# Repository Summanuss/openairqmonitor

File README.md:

# Open AirQ Monitor

## Table of Contents
- [Open AirQ Monitor](#open-airq-monitor)
  - [Table of Contents](#table-of-contents)
  - [Overview](#overview)
  - [Description](#description)
  - [Key Features](#key-features)
  - [Technical Specifications](#technical-specifications)
  - [Project Structure](#project-structure)
  - [Hardware Documentation](#hardware-documentation)
  - [Pinout \& Connectors](#pinout--connectors)
  - [Getting Started](#getting-started)
    - [Opening the KiCad project](#opening-the-kicad-project)
    - [Generating fabrication files](#generating-fabrication-files)
    - [Flashing the firmware](#flashing-the-firmware)
  - [Ordering \& Fabrication Guidelines](#ordering--fabrication-guidelines)
  - [Test Firmware](#test-firmware)
  - [Known Issues \& Future Improvements](#known-issues--future-improvements)
  - [Safety Notes](#safety-notes)
  - [Revision History](#revision-history)
  - [License](#license)
  - [Acknowledgments](#acknowledgments)
  - [Contact](#contact)

## Overview
- **Description:** STM32 based custom-board to monitor temperature, humidity and VOC
- **Status:** Stable - Revision 2.0
- **License:** Apache-2.0 license

## Description
Open AirQ Monitor is a very simple STM32 custom PCB with a temperature/humidity sensor and a
VOC sensor. It's goal is to be a consumer / gadget product which you can keep in your bedroom,
rather than a professional industrial solution to monitor ambient parameters.
Given that, I decided to use an LCD TFT RGB display so the firmware application can be more
"fancy" and "nice". <br>
As an hobbistic project, I wanted it to be as cheap and easy to design as possible. <br>
This can be seen as a starting point to build a more advanced product with more functionality,
so feel free to fork the repo and customize it as you like!

## Key Features
- LCD TFT [128x160 px] Display
- Dimmable display backlight
- USB-C powered (5V)
- Push-button as a general input or EXTI
- Real-time temperature and humidity measurement
- Real-time VOC measurement

## Technical Specifications
| Parameter | Value |
| :--- | :--- |
| **Input Voltage** | 5V |
| **Typical Current Draw** | **TODO** (e.g. ~xx mA idle / xx mA peak) |
| **Microcontroller / Core** | STM32L431CCT6TR |
| **Microcontroller / RAM** | 64 KB |
| **Microcontroller / FLASH** | 256 KB |
| **VOC Sensor** | SGP40-D-R4 |
| **Temp/Humidity Sensor** | SHT40-AD1B-R2 |
| **TFT Display** | ER-TFT018-3 |
| **Dimensions** | 60x40 mm |
| **Mounting Holes** | M2 |

## Project Structure
```text
├── docs/             # Documentation, schematics PDF, and renders
├── fabrication/      # Production files (Gerbers, BOM, Pick & Place)
├── design/           # KiCad project source files
├── exported          # .step, BOM, ...
├── LICENSE           # License file
└── README.md         # Project documentation
```

## Hardware Documentation
Check the docs/ folder.

## Pinout & Connectors
For the complete pinout check the schematic.
| Pin | Function | Description | Direction
| :--- | :--- | :--- | :--- |
| PA1 | SPI_CLK | SPI Clock Signal | Out |
| PA3 | BUTTON_IN | External Button Signal | In |
| PA4 | DC_DISPLAY | Data / Command Display Signal | Out |
| PA5 | RST_DISPLAY | Display Reset Signal | Out |
| PA6 | CS_DISPLAY | Display Chip Select Signal | Out |
| PA7 | SPI_MOSI | Display Serial Data Signal | Out |
| PA8 | BCK_LIGHT_DISPLAY | Display Backlight Signal | Out |
| PA9 | I2C_SCL | SCL Line of I2C bus | Out |
| PA10 | I2C_SDA | SDA Line of I2C bus | In / Out |
| PA11 | SWDIO | Serial Wire Data Signal | In / Out |
| PA14 | SWCLK | Serial Wire Protocol Clock Signal | In |
| PB3 | SWO | Serial Wire Protocol Output Signal | Out |

## Getting Started
 
### Opening the KiCad project
1. Install [KiCad 10.0](https://www.kicad.org/download/) or later.
2. Clone this repository.
3. Custom symbol files should be automatically embedded (KiCad versione > 6). If this is not the case, open an issue an I'll fix it ASAP.

### Generating fabrication files
1. Open the PCB editor in KiCad.
2. Export Gerbers, drill files, and Pick & Place using KiCad's built-in plotter (or the AISLER plugin, see [Ordering & Fabrication Guidelines](#ordering--fabrication-guidelines)).
3. Upload the generated files in your chosen manufacturer website (es. AISLER)
4. Check the correctness of the layout in the preview before ordering!

### Flashing the firmware
1. Connect an SWD programmer (e.g. ST-Link V2/V3) to the `SWDIO`/`SWCLK`/`SWO` pins.
2. Build and flash the firmware from the [Test Firmware](#test-firmware) repository following its own instructions.
3. Power the board via USB-C (5V) once flashing is complete.

## Ordering & Fabrication Guidelines
The chosen manufacturer is AISLER and every constraints in the layout that I used is based on their specifications.<br>
I used the AISLER plugin for KiCad to export all fabrication files. Just for reference, I created them manually in
fabrication directory. <br>
However, I didn't double checked those and a further analysis is suggested.
Also, the PCB was manually assembled by me and no assembly services were used from the manufacturer.

## Test Firmware
Test firmware written in C is provided [here](https://github.com/Summanuss/openairqmonitor_testfw.git) <br>
More information about it are provided in the linked repository.

## Known Issues & Future Improvements
- The SHT40 sensor is not perfectly thermally decoupled from the PCB and its reading can be a bit altered from the heat generated from the display and the rest of the PCB.
- The flashing and debugging pins are permanently soldered on the PCB which is not optimal.
<br>Ideas for revision 3.0:
- Correct the known issues.
- Provide the support for a battery powered device.

## Safety Notes
- The board is powered via USB-C at 5V - use a standard certified USB-C cable/power source.
- Use the SWD connector interface **ONLY** for flashing and debug.

## Revision History
- **v2.0:** Final and stable version
- **v1.0:** First working prototype

## License
Distributed under the Apache-2.0 License. See `LICENSE` for more information.

## Acknowledgments
I would like to thanks my friends which worked on the final firmware product and device enclouse:
- D.G.
- A.B.

## Contact
Mail: serafin.jacopo99@gmail.com

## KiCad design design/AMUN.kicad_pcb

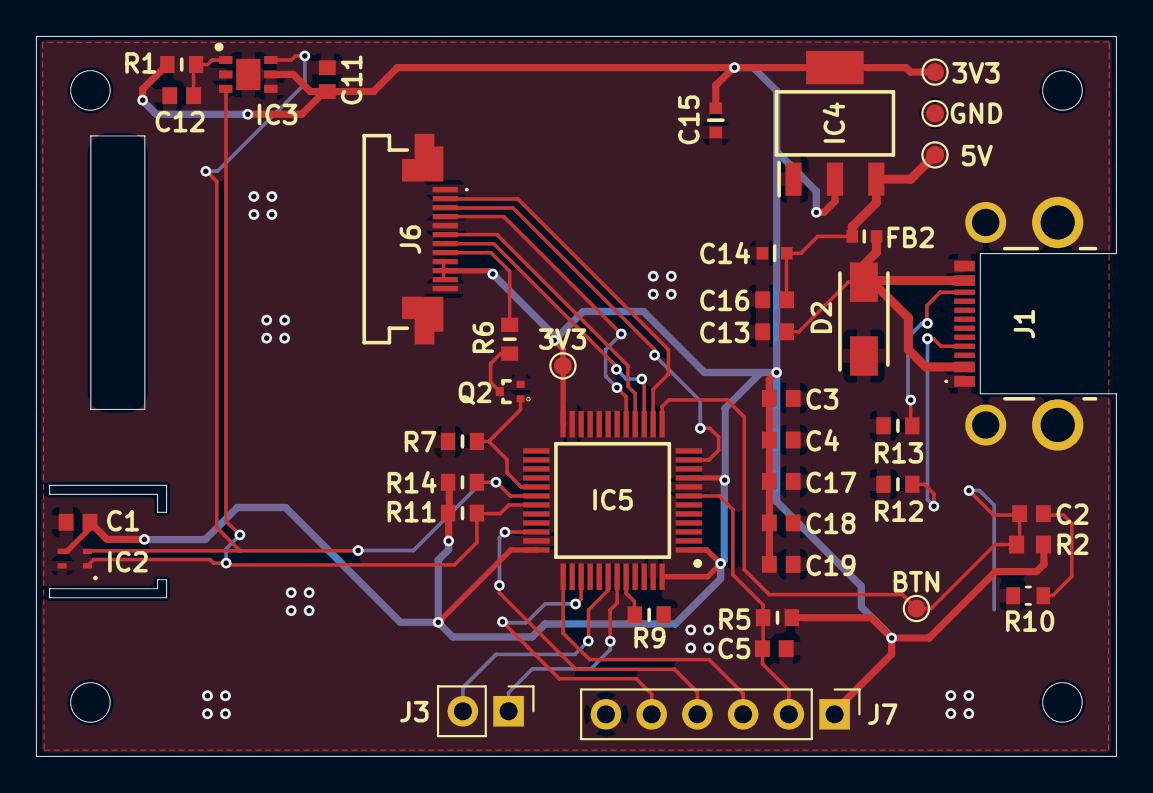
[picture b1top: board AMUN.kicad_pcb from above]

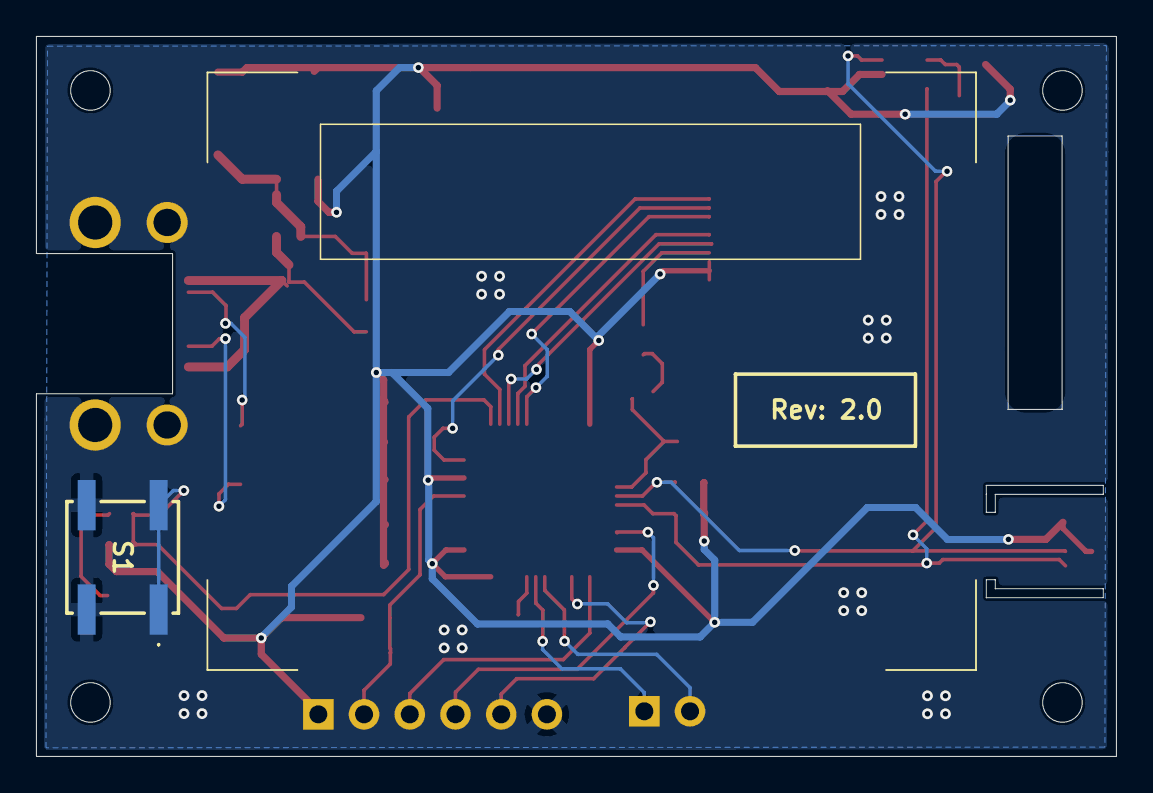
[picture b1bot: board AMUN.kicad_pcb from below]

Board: 2 copper layers, 60.0 x 40.0 mm, 47 parts (2 on the bottom side), 26 nets.

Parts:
3V3, 3V3#2: 3V3; TestPoint_Pad_D1.0mm
5V: 5V; TestPoint_Pad_D1.0mm
BTN: BTN; TestPoint_Pad_D1.0mm
C1, C2, C3, C4, C5, C17, C18, C19: 100nF; CAPC1608X90N
C11, C12: 1uF; CAPC1608X90N
C13, C16: 2.2uF; CAPC1608X90N
C14: 10uF; GRM18x
C15: 22uF; GRM18x
D2: SMAJ6.5CA_TR7; DIOM5127X250N
FB2: BLM18PG330SH1D; BLM18SP221SN1B
GND: GND; TestPoint_Pad_D1.0mm
H1, H2, H3, H4: MountingHole; MountingHole_2.2mm_M2_DIN965
IC2: SHT40-AD1B-R2; SHT40AD1BR2
IC3: SGP40-D-R4; SON80P244X244X95-7N
IC4: AZ1117CH-3.3TRG1; SOT230P700X180-4N
IC5: STM32L431CCT6TR; QFP50P900X900X160-48N
J1: UJ20-C-H-G-MSMT-4B-P16-TR; UJ20CHGMSMT4BP16TR
J3: Conn_01x02_Pin; PinHeader_1x02_P2.54mm_Vertical
J6: SFV12R-1STBE1HLF; SFV12R1STBE1HLF
J7: Conn_01x06; PinHeader_1x06_P2.54mm_Vertical
Q2: SSM3K16FV,L3F; VESM_SOT-723_
R1: RC0603FR-134R7L; RESC1608X55N
R2: 4.7K; RESC1608X50N
R5, R7, R9, R11, R14: 10K; RESC1608X55N
R6: 10; RESC1608X55N
R10: 100; RESC1608X60N
R12, R13: 5.1K; RESC1608X55N
S1: EL2_52_35J_LFS; EL25235JLFS
U2: ER-TFT018-3

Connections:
+3V3: 3V3.1 (1_1), 3V3#2.1 (1_1), C1.1, C3.1, C4.1, C11.1, C15.1, C17.1, C18.1, C19.1, IC2.3 (VDD), IC3.5 (VDDH), IC4.2 (OUTPUT), IC4.4 (VOUT), IC5.1 (VBAT), IC5.9 (VDDA/VREF+), IC5.24 (VDD_1), IC5.36 (VDD_2), IC5.48 (VDD_3), J6.9, J6.10, J6.11, J7.1, R1.2, R2.2, R5.2, R11.2, R14.2
+5V: 5V.1 (1_1), C14.1, C16.1, FB2.2, IC4.3 (INPUT)
/BCK_LIGHT: IC5.29 (PA8), Q2.1 (G), R7.1
/CS_DISPLAY: IC5.16 (PA6), J6.6
/DC_DISPLAY: IC5.14 (PA4), J6.2
/Display/LEDK: J6.8, R6.2
/I2C_SCL: IC2.2 (SCL), IC3.6 (SCL), IC5.30 (PA9), R14.1
/I2C_SDA: IC2.1 (SDA), IC3.3 (SDA), IC5.31 (PA10), R11.1
/MCU/BUTTON: BTN.1 (1_1), C2.1, IC5.13 (PA3), R2.1, S1.1 (COM_1), S1.2 (COM_2)
/MCU/MCU_BOOT0: IC5.44 (PH3/BOOT0), R9.2
/MCU/MCU_NRST: C5.1, IC5.7 (NRST), J7.2, R5.1
/MCU/MCU_SWCLK: IC5.37 (PA14), J7.3
/MCU/MCU_SWDIO: IC5.34 (PA13), J7.4
/MCU/MCU_SWO: IC5.39 (PB3), J7.5
/MCU/USART_RX_DEVELOP: IC5.43 (PB7), J3.1
/MCU/USART_TX_DEVELOP: IC5.42 (PB6), J3.2
/RST_DISPLAY: IC5.15 (PA5), J6.7
/SPI_CLK: IC5.11 (PA1), J6.3
/SPI_MOSI: IC5.17 (PA7), J6.4
GND: C1.2, C3.2, C4.2, C5.2, C11.2, C12.2, C13.2, C14.2, C15.2, C16.2, C17.2, C18.2, C19.2, D2.1, GND.1 (1_1), IC2.4 (VSS), IC3.2 (VSS), IC3.4 (N/A), IC3.7 (EP), IC4.1 (ADJ/GND), IC5.8 (VSSA/VREF-), IC5.23 (VSS_1), IC5.35 (VSS_2), IC5.47 (VSS_3), J1.A1 (GND_1), J1.B1 (GND_2), J6.1, J6.5, J6.12, J7.6, Q2.2 (S), R7.2, R9.1, R10.2 (R2), R12.2, R13.2, S1.3 (NO_1), S1.4 (NO_2)
unnamed: C12.1, IC3.1 (VDD), R1.1
unnamed: J1.A5 (CC1), R12.1
unnamed: J1.B5 (CC2), R13.1
unnamed: C13.1, D2.2, FB2.1, J1.A4 (VBUS_1), J1.B4 (VBUS_2)
unnamed: Q2.3 (D), R6.1
unnamed: C2.2, R10.1 (R1)

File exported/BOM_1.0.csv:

"Reference","Value","Datasheet","Footprint","Qty","DNP","Manufacturer_Name","Manufacturer_Part_Number","Mouser Part Number","Descrizione"
"C1,C2,C3,C4,C5,C17,C18,C19","100nF","https://datasheet.datasheetarchive.com/originals/distributor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","amun_lib:CAPC1608X90N","8","","Yageo Group","CC0603ZRY5V7BB104","603-CC603ZRY5V7BB104","YAGEO - CC0603ZRY5V7BB104 - CERAMIC CAPACITOR, 0.1UF, 16V, Y5V, +80,-20%, 0603"
"C11,C12","1uF","","amun_lib:CAPC1608X90N","2","","SAMSUNG","CL10B105KP8NFNC","187-CL10B105KP8NFNC","General Multilayer Ceramic Capacitors"
"C13,C16","2.2uF","https://datasheet.datasheetarchive.com/originals/distributor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","amun_lib:CAPC1608X90N","2","","SAMSUNG","CL10A225KP8NNNC","187-CL10A225KP8NNNC","Samsung Electro-Mechanics 0603 CL 2.2uF Ceramic Multilayer Capacitor, 10 V, +85C, X5R Dielectric, +/-10% SMD"
"C14","10uF","https://search.murata.co.jp/Ceramy/image/img/A01X/G101/ENG/G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","amun_lib:GRM18x","1","","Murata Electronics","GRM188R61A106ME69J","81-GRM188R61A106ME9J","MLCC, 0603"
"C15","22uF","https://search.murata.co.jp/Ceramy/image/img/A01X/G101/ENG/G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","amun_lib:GRM18x","1","","Murata Electronics","GRM187R61A226ME15D","81-GRM187R61A226ME5D","MLCC, 0603"
"D2","SMAJ6.5CA_TR7","https://www.mouser.it/datasheet/3/508/1/SMAJ_1.pdf","amun_lib:DIOM5127X250N","1","","Yageo Group","SMAJ6.5CA/TR7","603-SMAJ6.5CA/TR7","ESD Protection Diodes / TVS Diodes SMAJ - CA         6.5V"
"FB2","BLM18PG330SH1D","http://www.murata.com/~/media/webrenewal/support/library/cat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","amun_lib:BLM18SP221SN1B","1","","Murata Electronics","BLM18PG330SH1D","81-BLM18PG330SH1D","Murata Power Solutions Ferrite Bead (Chip Bead), 1.6 x 0.8 x 0.8mm (1608), 33 impedance at 100 MHz"
"IC2","SHT40-AD1B-R2","https://www.digikey.com/en/products/detail/sensirion-ag/SHT4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","amun_lib:SHT40AD1BR2","1","","Sensirion","SHT40-AD1B-R2","403-SHT40-AD1B-R2","4th Generation, High-Accuracy, Ultra Low Power, 16-Bit Relative Humidity and Temperature Sensor Platform"
"IC3","SGP40-D-R4","https://www.mouser.it/datasheet/3/1278/1/Sensirion_Gas_Senso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","amun_lib:SON80P244X244X95-7N","1","","Sensirion","SGP40-D-R4","403-SGP40-D-R4","Air Quality Sensors Gas Sensor 2.5k pcs IC"
"IC4","AZ1117CH-3.3TRG1","https://www.diodes.com//assets/Datasheets/AZ1117C.pdf","amun_lib:SOT230P700X180-4N","1","","Diodes Incorporated","AZ1117CH-3.3TRG1","621-AZ1117CH-3.3TRG1","1.35A 3.3V LDO Reg. Current Limit SOT223 DiodesZetex AZ1117CH-3.3TRG1, LDO Voltage Regulator, 0.8A, 3.3 V +/-1%, maximum of 15 Vin, 3-Pin SOT-223"
"IC5","STM32L431CCT6TR","https://www.st.com/resource/en/datasheet/stm32l431cb.pdf","amun_lib:QFP50P900X900X160-48N","1","","STMicroelectronics","STM32L431CCT6TR","511-STM32L431CCT6TR","Ultra-low-power Arm Cortex-M4 32-bit MCU+FPU, 100DMIPS, up to 256KB Flash, 64KB SRAM, analog, audio"
"J1","UJ20-C-H-G-MSMT-4B-P16-TR","https://www.sameskydevices.com/product/resource/uj20-c-h-g-m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","amun_lib:UJ20CHGMSMT4BP16TR","1","","Same Sky","UJ20-C-H-G-MSMT-4B-P16-TR","","Type C, USB 2.0, 480 Mbps, 20 Vdc, 3 A, Horizontal, Mid Mount SMT, SMT Contacts, Gold Flash, 16 Pins, USB Receptacle"
"J6","SFV12R-1STBE1HLF","https://cdn.amphenol-cs.com/media/wysiwyg/files/drawing/sfv1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","amun_lib:SFV12R1STBE1HLF","1","","Amphenol Communications Solutions","SFV12R-1STBE1HLF","","0.50mm Flex Connector, SFV-R Series, 12 Position, Bottom Side Contact, Side Entry Surface Mount ZIF Connector, Halogen Free, Lead Free, Gold Flash."
"Q2","SSM3K16FV,L3F","http://toshiba.semicon-storage.com/info/docget.jsp?did=591&p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","amun_lib:VESM_SOT-723_","1","","Toshiba","SSM3K16FV,L3F","757-SSM3K16FVL3F","MOSFET LowON Res MOSFET ID=0.1A VDSS=20V"
"R1","RC0603FR-134R7L","https://componentsearchengine.com/Datasheets/1/RC0603FR-134R7L.pdf","amun_lib:RESC1608X55N","1","","Yageo Group","RC0603FR-134R7L","603-RC0603FR-134R7L","Thick Film Resistors - SMD 4.7 OHM 1%"
"R2","4.7K","http://www.vishay.com/docs/20035/dcrcwe3.pdf","amun_lib:RESC1608X50N","1","","Vishay","CRCW06034K70FKEC","71-CRCW06034K70FKEC","Thick Film Resistors - SMD 4.7K  OHM   1%"
"R5,R7,R9,R11,R14","10K","https://componentsearchengine.com/Datasheets/1/RT0603DRD0710KL.pdf","amun_lib:RESC1608X55N","5","","Yageo Group","RT0603DRD0710KL","603-RT0603DRD0710KL","Resistor,Thin Film Resistors - SMD 10K Ohm 0.5% 1/10W 75 Volts 25ppm"
"R6","10","https://componentsearchengine.com/Datasheets/1/RC0603FR-7W10RL.pdf","amun_lib:RESC1608X55N","1","","Yageo Group","RC0603FR-7W10RL","603-RC0603FR-7W10RL","RESISTOR, 0603 10 Ohms +/-1% 1/10 W"
"R10","100","https://componentsearchengine.com/Datasheets/1/RT0603FRE07100RL.pdf","amun_lib:RESC1608X60N","1","","Yageo Group","RT0603FRE07100RL","603-RT0603FRE07100RL","RESISTOR, 0603 100 Ohms +/-1% 1/10 W"
"R12,R13","5.1K","http://www.yageo.com/documents/recent/PYu-RC0603_51_RoHS_L_v5.pdf","amun_lib:RESC1608X55N","2","","Yageo Group","RC0603FR-135K1L","603-RC0603FR-135K1L","Thick Film Resistors - SMD 5.1K OHM 1%"
"S1","EL2_52_35J_LFS","https://www.littelfuse.com/assetdocs/littelfuse-c-k-tactile-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","amun_lib:EL25235JLFS","1","","LITTELFUSE","EL2 52 35J LFS","611-EL25235JLFS","Tactile Switches 6.2x6.2x5.2mm 3.5N Operating Force -40C to 85C,150 mA"
